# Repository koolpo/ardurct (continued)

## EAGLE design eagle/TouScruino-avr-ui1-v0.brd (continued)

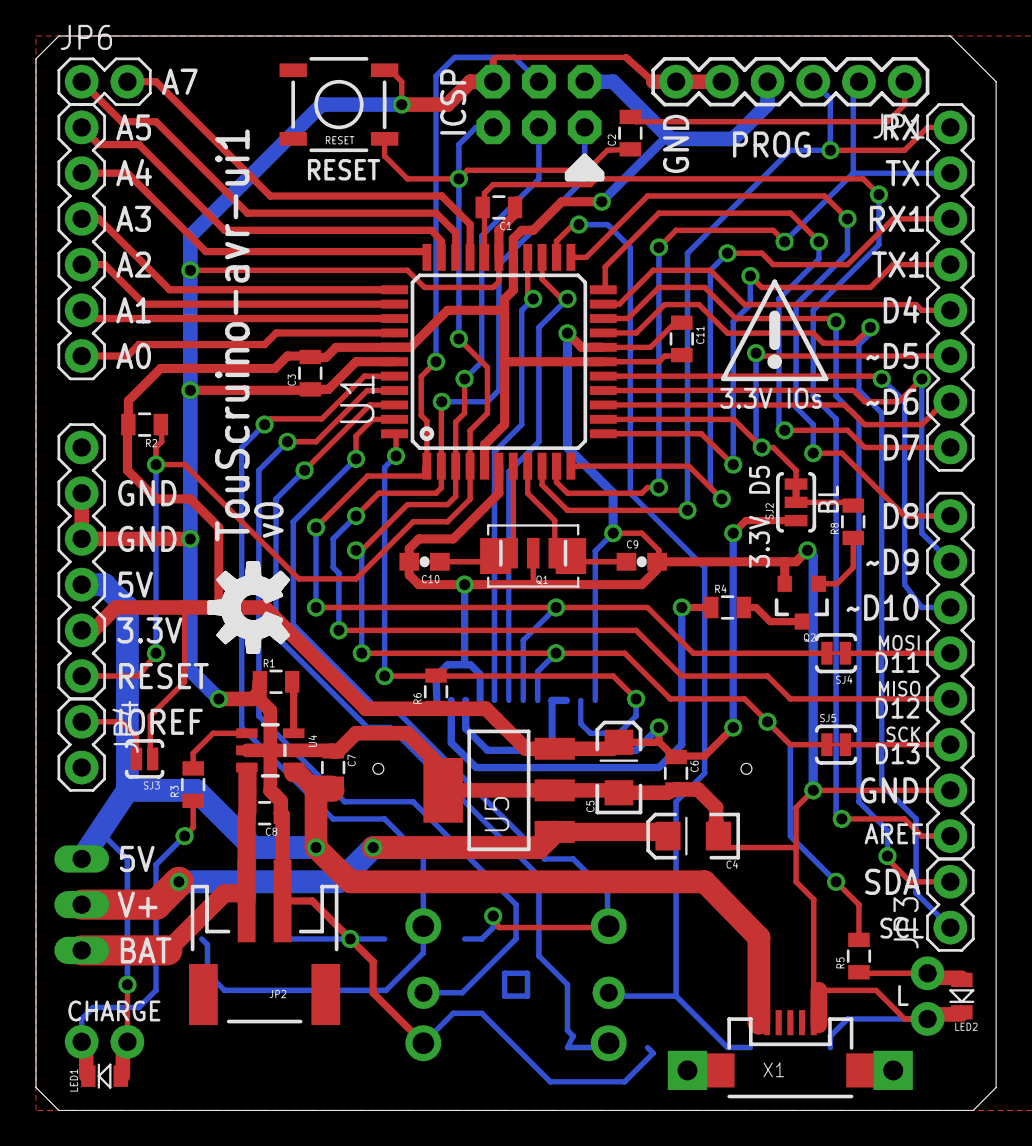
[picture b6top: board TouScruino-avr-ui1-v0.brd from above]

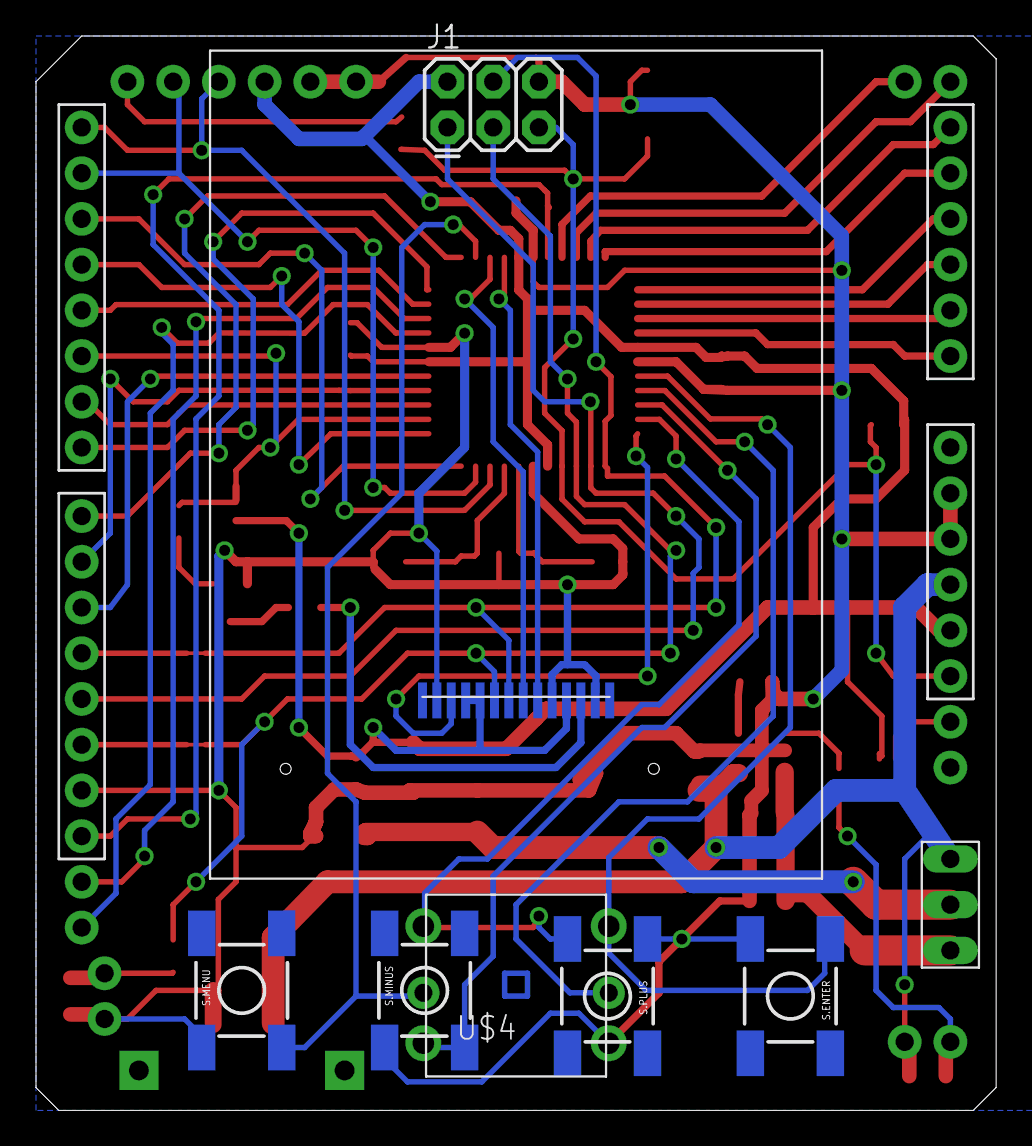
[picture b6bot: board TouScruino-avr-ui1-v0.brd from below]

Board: 2 copper layers, 53.3 x 59.7 mm, 49 parts (9 on the bottom side), 53 nets.

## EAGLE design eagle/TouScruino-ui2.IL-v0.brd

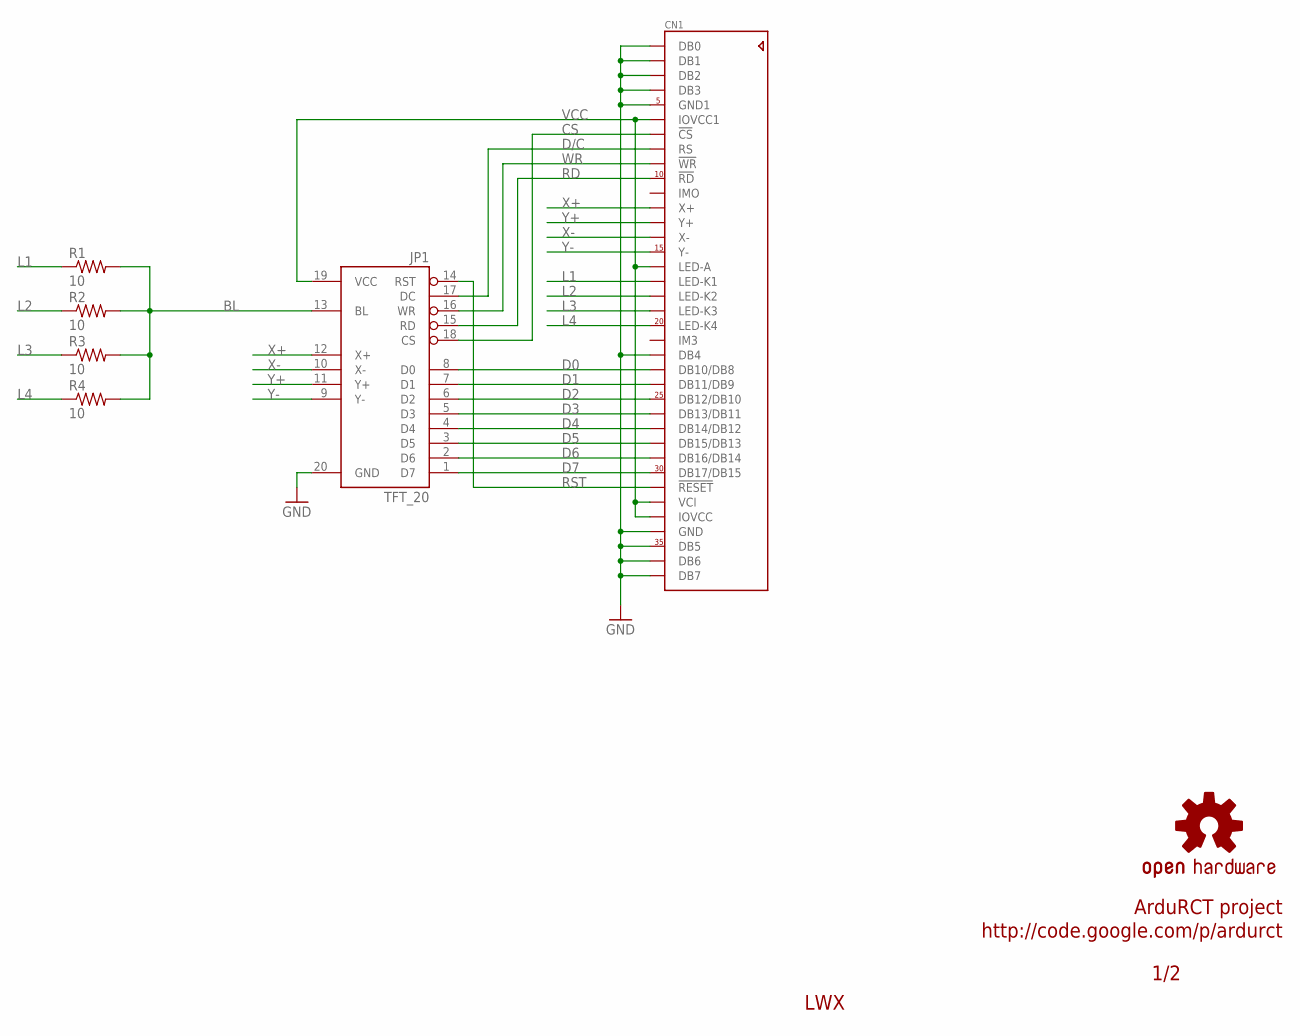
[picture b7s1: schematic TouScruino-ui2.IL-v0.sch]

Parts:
CN1: ILI9325_LCD1.0MM; ILI9325_28INCH_TS
JP1: TFT_20
R1, R2, R3, R4: 10; R0603
U$3: OSHW-LOGOM; OSHW-LOGO-M

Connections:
BL: JP1.13 (BL), R1.2, R2.2, R3.2, R4.2
CS: CN1.7 (!CS), JP1.18 (CS)
D0: CN1.23 (DB10/DB8), JP1.8 (D0)
D1: CN1.24 (DB11/DB9), JP1.7 (D1)
D2: CN1.25 (DB12/DB10), JP1.6 (D2)
D3: CN1.26 (DB13/DB11), JP1.5 (D3)
D4: CN1.27 (DB14/DB12), JP1.4 (D4)
D5: CN1.28 (DB15/DB13), JP1.3 (D5)
D6: CN1.29 (DB16/DB14), JP1.2 (D6)
D7: CN1.30 (DB17/DB15), JP1.1 (D7)
D/C: CN1.8 (RS), JP1.17 (DC)
GND: CN1.1 (DB0), CN1.2 (DB1), CN1.3 (DB2), CN1.4 (DB3), CN1.5 (GND1), CN1.22 (DB4), CN1.34 (GND), CN1.35 (DB5), CN1.36 (DB6), CN1.37 (DB7), JP1.20 (GND)
L1: CN1.17 (LED-K1), R1.1
L2: CN1.18 (LED-K2), R2.1
L3: CN1.19 (LED-K3), R3.1
L4: CN1.20 (LED-K4), R4.1
RD: CN1.10 (!RD), JP1.15 (RD)
RST: CN1.31 (!RESET), JP1.14 (RST)
VCC: CN1.6 (IOVCC1), CN1.16 (LED-A), CN1.32 (VCI), CN1.33 (IOVCC), JP1.19 (VCC)
WR: CN1.9 (!WR), JP1.16 (WR)
X+: CN1.12 (X+), JP1.12 (X+)
X-: CN1.14 (X-), JP1.10 (X-)
Y+: CN1.13 (Y+), JP1.11 (Y+)
Y-: CN1.15 (Y-), JP1.9 (Y-)

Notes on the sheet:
LWX
1/2
ArduRCT project
http://code.google.com/p/ardurct

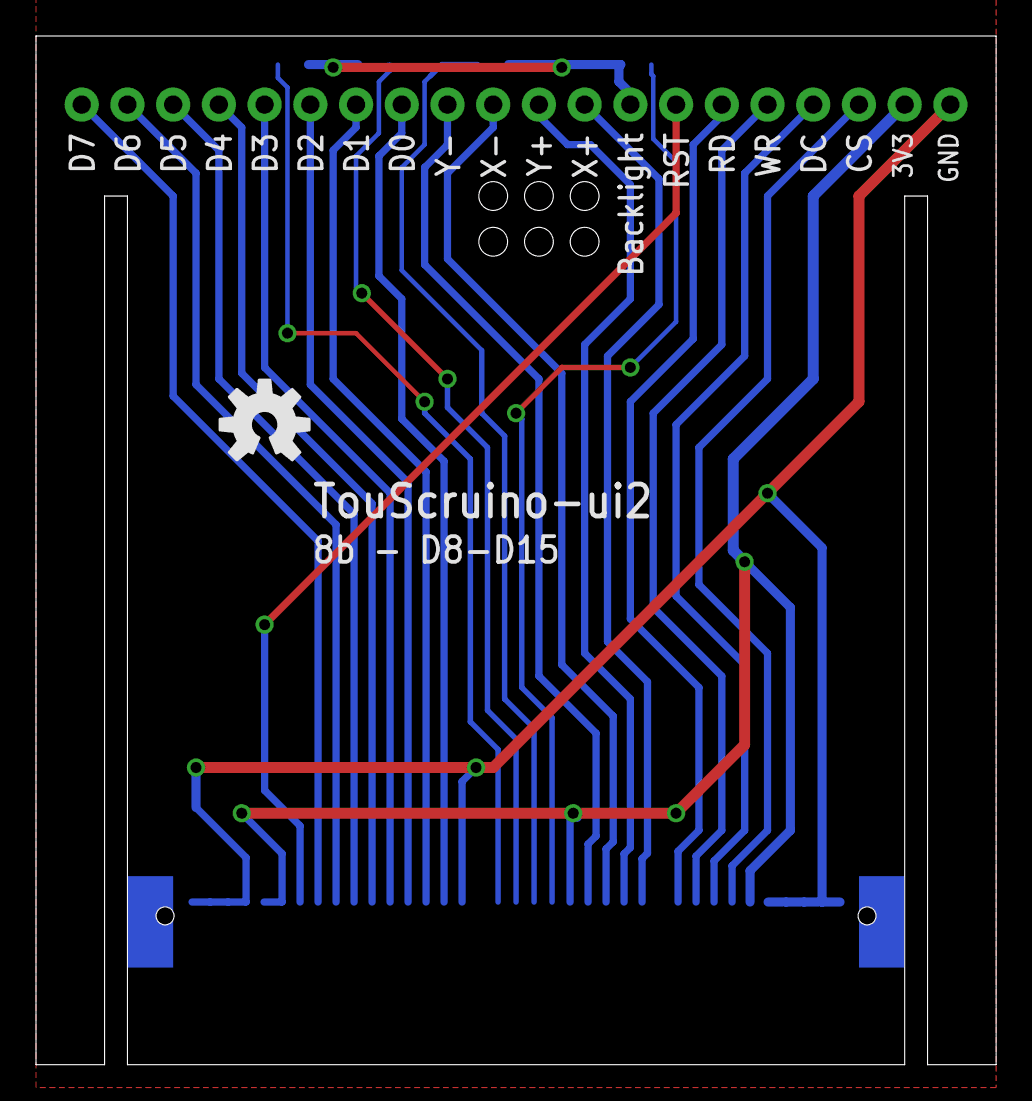
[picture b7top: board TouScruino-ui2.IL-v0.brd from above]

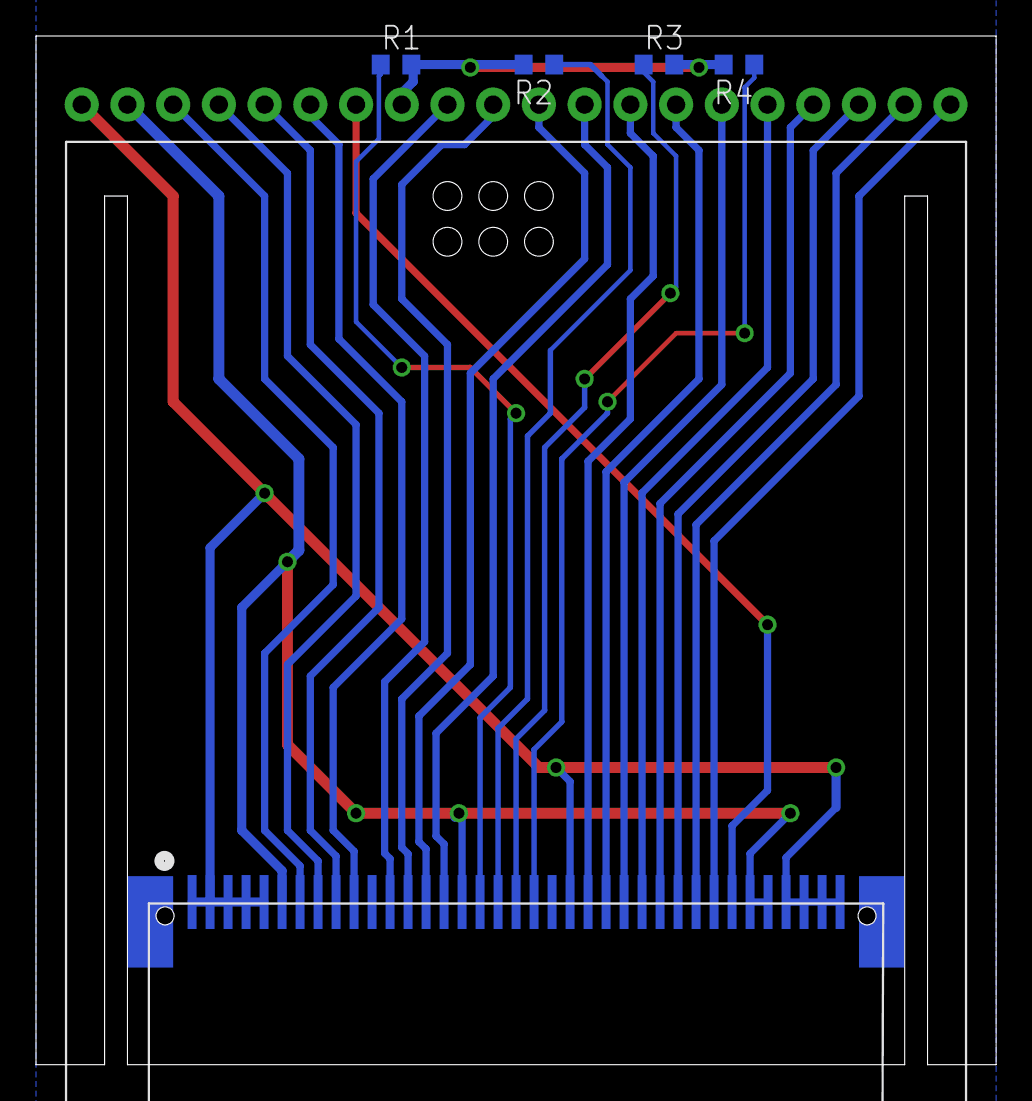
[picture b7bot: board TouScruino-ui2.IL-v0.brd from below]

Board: 2 copper layers, 53.3 x 57.1 mm, 7 parts (6 on the bottom side), 24 nets.

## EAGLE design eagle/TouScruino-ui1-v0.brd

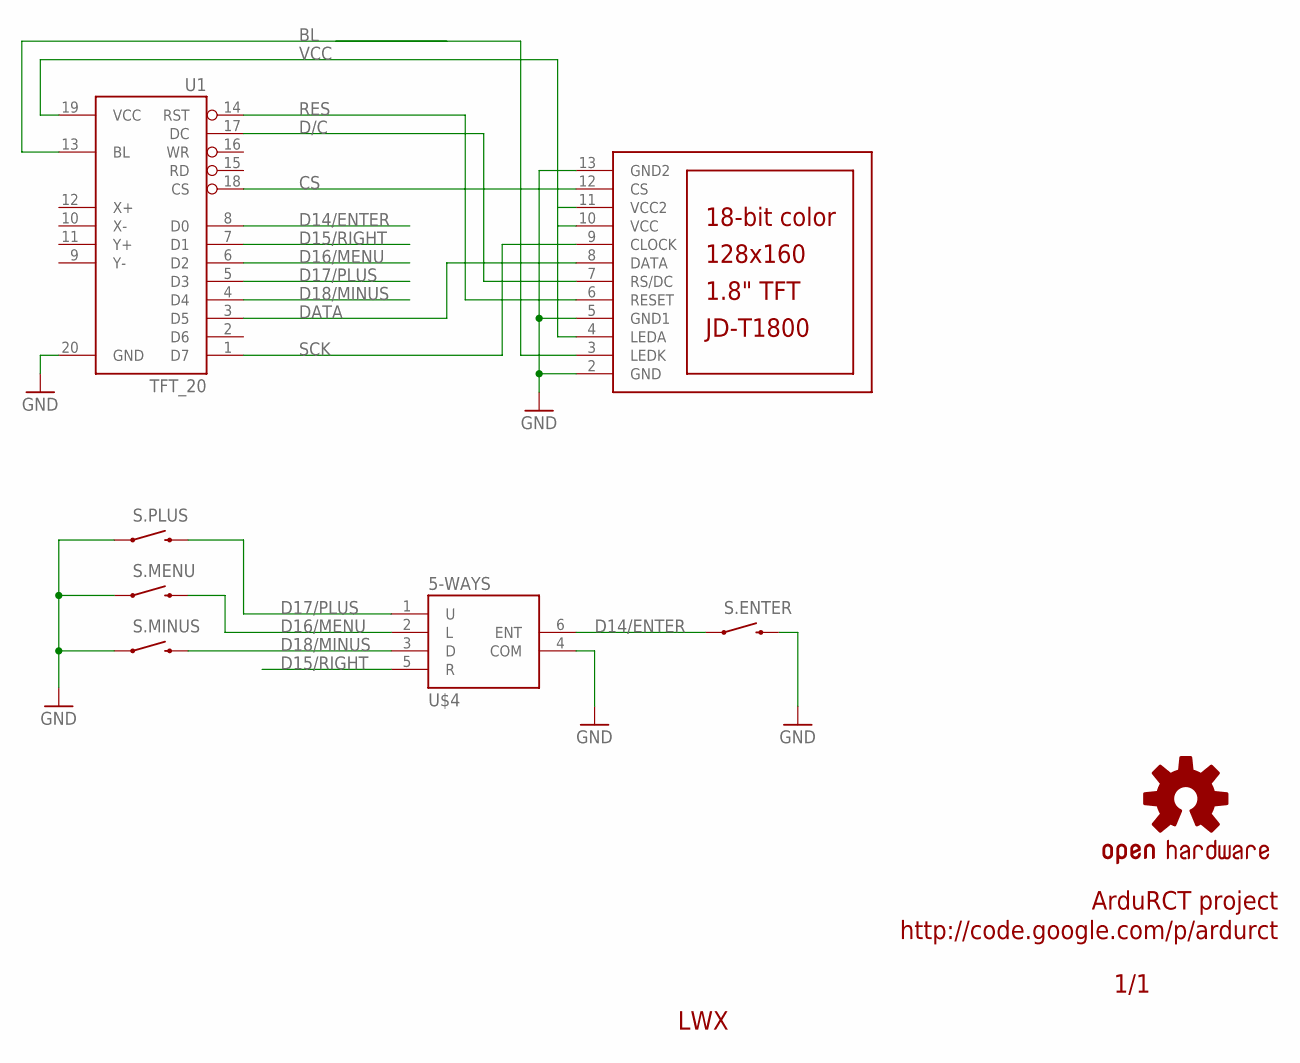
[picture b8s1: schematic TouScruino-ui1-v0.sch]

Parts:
LCD1: JD-T1800
S.ENTER, S.MENU, S.MINUS, S.PLUS: SWITCH_SMD; TACTILE_SWITCH_SMD
U1: TFT_20
U$3: OSHW-LOGOM; OSHW-LOGO-M
U$4: 5-WAYS; 5-WAYS_ALPS

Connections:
BL: LCD1.3 (LEDK), U1.13 (BL)
CS: LCD1.12 (CS), U1.18 (CS)
D14/ENTER: S.ENTER.1, U1.8 (D0), U$4.6 (ENT)
D15/RIGHT: U1.7 (D1), U$4.5 (R)
D16/MENU: S.MENU.3 (2), U1.6 (D2), U$4.2 (L)
D17/PLUS: S.PLUS.3 (2), U1.5 (D3), U$4.1 (U)
D18/MINUS: S.MINUS.3 (2), U1.4 (D4), U$4.3 (D)
D/C: LCD1.7 (RS/DC), U1.17 (DC)
DATA: LCD1.8 (DATA), U1.3 (D5)
GND: LCD1.2 (GND), LCD1.5 (GND1), LCD1.13 (GND2), S.ENTER.3 (2), S.MENU.1, S.MINUS.1, S.PLUS.1, U1.20 (GND), U$4.4 (COM)
RES: LCD1.6 (RESET), U1.14 (RST)
SCK: LCD1.9 (CLOCK), U1.1 (D7)
VCC: LCD1.4 (LEDA), LCD1.10 (VCC), LCD1.11 (VCC2), U1.19 (VCC)

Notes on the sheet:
LWX
1/1
ArduRCT project
http://code.google.com/p/ardurct

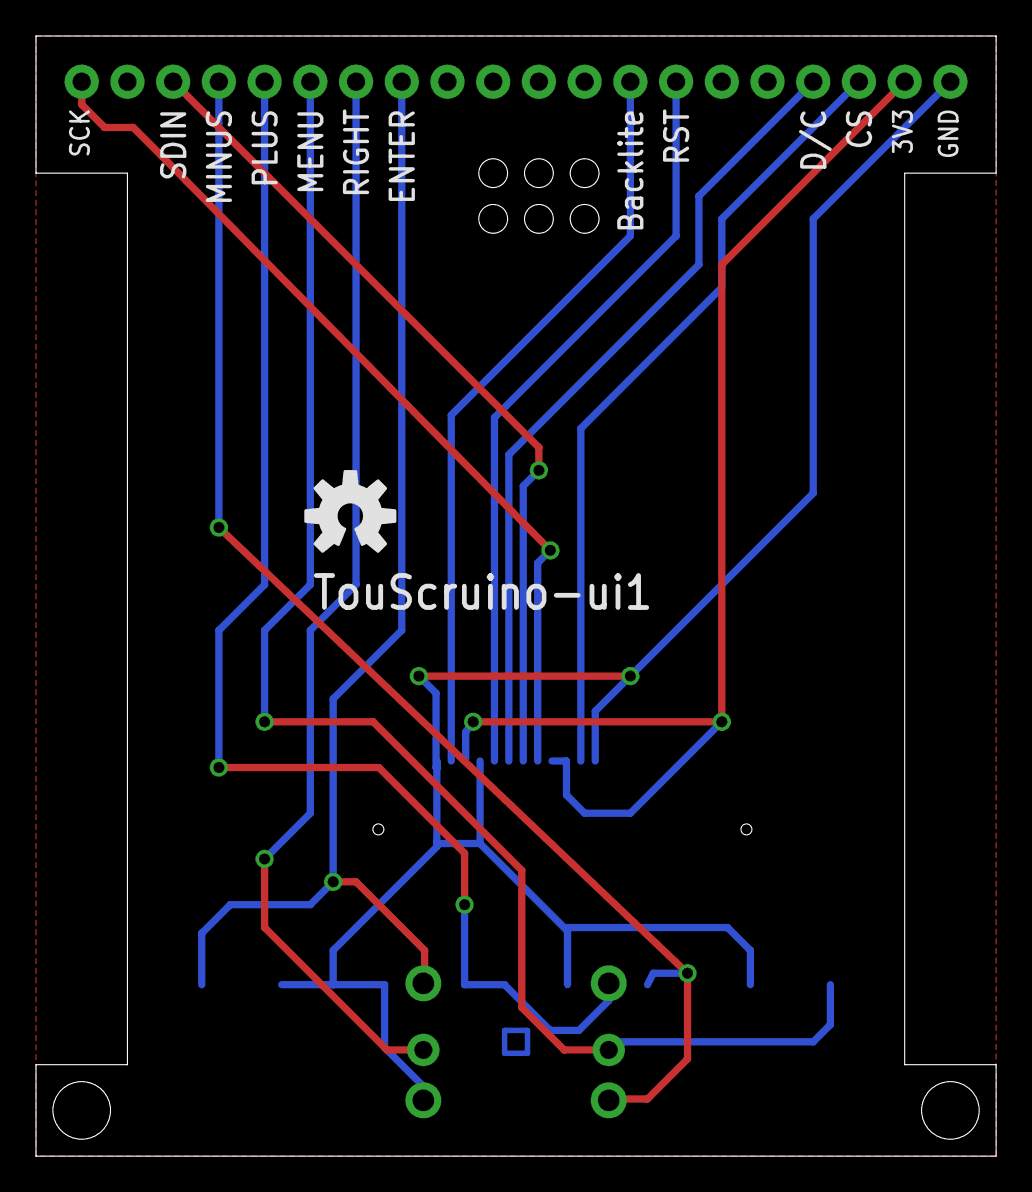
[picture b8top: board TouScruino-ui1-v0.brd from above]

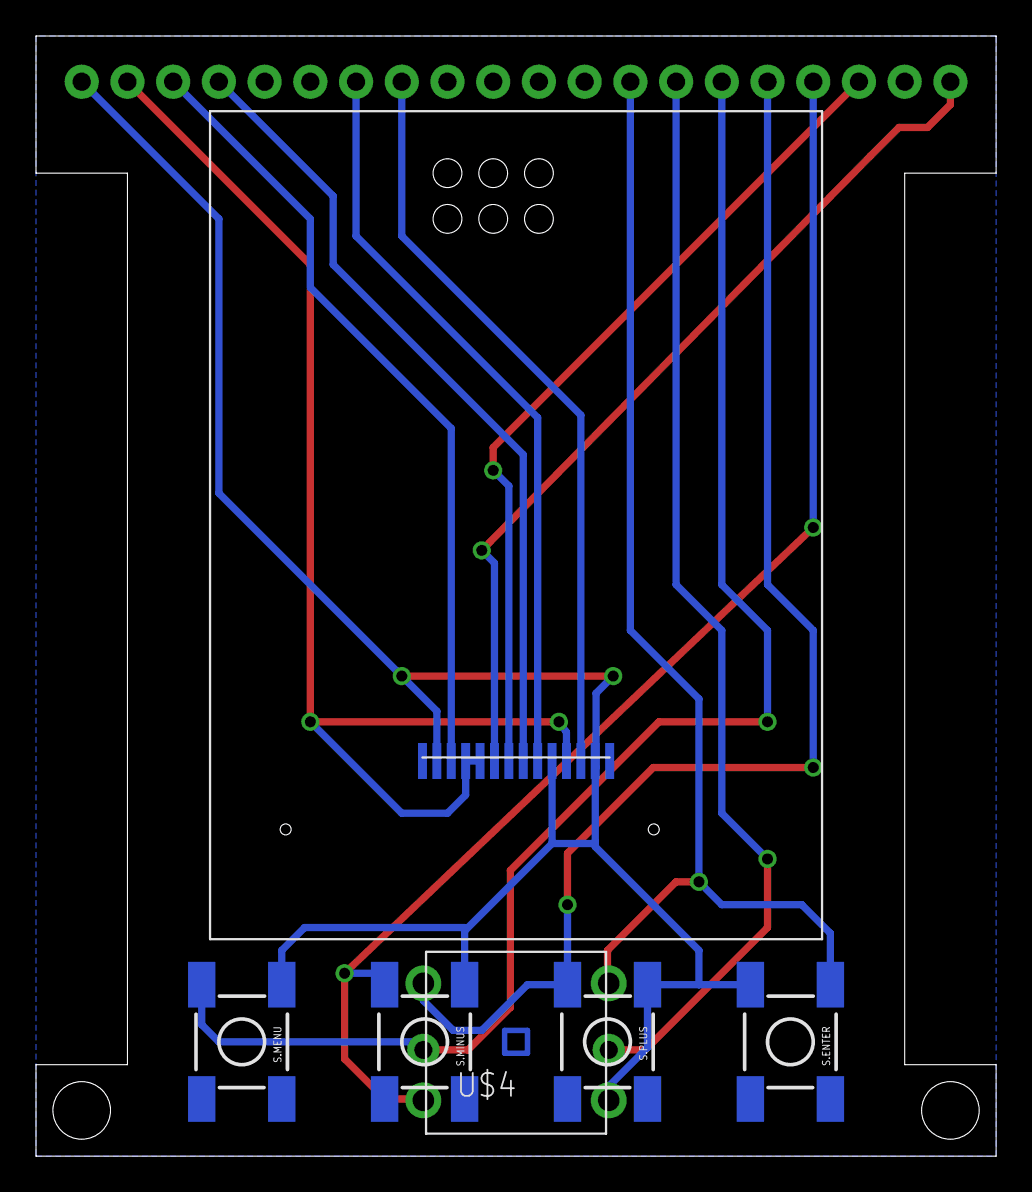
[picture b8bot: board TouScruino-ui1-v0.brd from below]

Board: 2 copper layers, 53.3 x 62.2 mm, 8 parts (7 on the bottom side), 13 nets.

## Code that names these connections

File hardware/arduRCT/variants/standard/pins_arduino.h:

/*
  pins_arduino.h - Pin definition functions for Arduino
  Part of Arduino - http://www.arduino.cc/

  Copyright (c) 2007 David A. Mellis

  This library is free software; you can redistribute it and/or
  modify it under the terms of the GNU Lesser General Public
  License as published by the Free Software Foundation; either
  version 2.1 of the License, or (at your option) any later version.

  This library is distributed in the hope that it will be useful,
  but WITHOUT ANY WARRANTY; without even the implied warranty of
  MERCHANTABILITY or FITNESS FOR A PARTICULAR PURPOSE.  See the GNU
  Lesser General Public License for more details.

  You should have received a copy of the GNU Lesser General
  Public License along with this library; if not, write to the
  Free Software Foundation, Inc., 59 Temple Place, Suite 330,
  Boston, MA  02111-1307  USA

  $Id: wiring.h 249 2007-02-03 16:52:51Z mellis $
*/

#ifndef Pins_Arduino_h
#define Pins_Arduino_h

#include <avr/pgmspace.h>

#define NUM_DIGITAL_PINS            32
#define NUM_ANALOG_INPUTS           8
#define analogInputToDigitalPin(p)  ((p < 8) ? (p) + 24 : -1)
#define digitalPinHasPWM(p)         ((p) == 5 || (p) == 6 || (p) == 9 || (p) == 10 || (p) == 11 || (p) == 17 || (p) == 18)

const static uint8_t SS   = 18;
const static uint8_t MOSI = 11;
const static uint8_t MISO = 12;
const static uint8_t SCK  = 13;

const static uint8_t SDA = 20;
const static uint8_t SCL = 19;
const static uint8_t LED_BUILTIN = 13;

const static uint8_t A0 = 24;
const static uint8_t A1 = 25;
const static uint8_t A2 = 26;
const static uint8_t A3 = 27;
const static uint8_t A4 = 28;
const static uint8_t A5 = 29;
const static uint8_t A6 = 30;
const static uint8_t A7 = 31;

// Only pins available for RECEIVE (TRANSMIT can be on any pin):
// I've deliberately left out pin mapping to the Hardware USARTs
// and also the analog pins: that already makes for 20 RECEIVE pins !

#define digitalPinToPCICR(p)    (((p) >= 4 && (p) <= 23) ? (&PCICR) : ((uint8_t *)0))
#define digitalPinToPCICRbit(p) ( ((p) == 5 || (p) == 6 || (p) == 9 || (p) == 10) ? 3 : \
								( ((p) >= 11 && (p) <= 18) ? 1 : 2 ))
#define digitalPinToPCMSK(p)    ( ((p) == 5 || (p) == 6 || (p) == 9 || (p) == 10) ? (&PCMSK3) : \
								( ((p) >= 11 && (p) <= 18) ? (&PCMSK1) : \
								( ((p) >= 4 && (p) <= 23) ?	(&PCMSK2) : ((uint8_t *)0) )))
#define digitalPinToPCMSKbit(p) ( ((p) == 5 || (p) == 6) ? (p)-1 : \
								( ((p) == 9 || (p) == 10) ? (p)-3 : \
								( ((p) == 4) ? (p)-2 : \
								( ((p) == 7 || (p) == 8) ? (p)-4 : \
								( ((p) >= 11 || (p) <= 13) ? (p)-6 : \
								( ((p) >= 14 || (p) <= 18) ? (p)-14 : \
								( ((p) == 19 || (p) == 20) ? (p)-19 : \
								( ((p) >= 21 || (p) <= 23) ? (p)-16 : 0) )))))))

#ifdef ARDUINO_MAIN

// these arrays map port names (e.g. port B) to the
// appropriate addresses for various functions (e.g. reading
// and writing)
const uint16_t PROGMEM port_to_mode_PGM[] = {
	NOT_A_PORT,
	(uint16_t) &DDRA,
	(uint16_t) &DDRB,
	(uint16_t) &DDRC,
	(uint16_t) &DDRD,
};

const uint16_t PROGMEM port_to_output_PGM[] = {
	NOT_A_PORT,
	(uint16_t) &PORTA,
	(uint16_t) &PORTB,
	(uint16_t) &PORTC,
	(uint16_t) &PORTD,
};

const uint16_t PROGMEM port_to_input_PGM[] = {
	NOT_A_PORT,
	(uint16_t) &PINA,
	(uint16_t) &PINB,
	(uint16_t) &PINC,
	(uint16_t) &PIND,
};

const uint8_t PROGMEM digital_pin_to_port_PGM[] = {
	PD,		// PD0 -  D0 / RX
	PD,		// PD1 -  D1 / TX
	PD,		// PD2 -  D2 / RX2
	PD,		// PD3 -  D3 / TX2
	PC,		// PC2 -  D4
	PD,		// PD4 -  D5 / PWM1
	PD,		// PD5 -  D6 / PWM2
	PC,		// PC3 -  D7
	PC,		// PC4 -  D8
	PD,		// PD6 -  D9 / PWM3
	PD,		// PD7 - D10 / PWM4
	PB,		// PB5 - D11 / MOSI
	PB,		// PB6 - D12 / MISO
	PB,		// PB7 - D13 / SCK / LED_BUILTIN
	PB,		// PB0 - D14
	PB,		// PB1 - D15
	PB,		// PB2 - D16
	PB,		// PB3 - D17 / PWM5
	PB,		// PB4 - D18 / PWM6 / SS
	PC,		// PC0 - D19 / SCL
	PC,		// PC1 - D20 / SDA
	PC,		// PC5 - D21
	PC,		// PC6 - D22
	PC,		// PC7 - D23
	PA,		// PA0 - D24 / A0
	PA,		// PA1 - D25 / A1
	PA,		// PA2 - D26 / A2
	PA,		// PA3 - D27 / A3
	PA,		// PA4 - D28 / A4
	PA,		// PA5 - D29 / A5
	PA,		// PA6 - D30 / A6
	PA,		// PA7 - D31 / A7
};

const uint8_t PROGMEM digital_pin_to_bit_mask_PGM[] = {
	_BV(0),		// PD0 -  D0 / RX
	_BV(1),		// PD1 -  D1 / TX
	_BV(2),		// PD2 -  D2 / RX2
	_BV(3),		// PD3 -  D3 / TX2
	_BV(2),		// PC2 -  D4
	_BV(4),		// PD4 -  D5 / PWM1
	_BV(5),		// PD5 -  D6 / PWM2
	_BV(3),		// PC3 -  D7
	_BV(4),		// PC4 -  D8
	_BV(6),		// PD6 -  D9 / PWM3
	_BV(7),		// PD7 - D10 / PWM4
	_BV(5),		// PB5 - D11 / MOSI
	_BV(6),		// PB6 - D12 / MISO
	_BV(7),		// PB7 - D13 / SCK / LED_BUILTIN
	_BV(0),		// PB0 - D14
	_BV(1),		// PB1 - D15
	_BV(2),		// PB2 - D16
	_BV(3),		// PB3 - D17 / PWM5
	_BV(4),		// PB4 - D18 / PWM6 / SS
	_BV(0),		// PC0 - D19 / SCL
	_BV(1),		// PC1 - D20 / SDA
	_BV(5),		// PC5 - D21
	_BV(6),		// PC6 - D22
	_BV(7),		// PC7 - D23
	_BV(0),		// PA0 - D24 / A0
	_BV(1),		// PA1 - D25 / A1
	_BV(2),		// PA2 - D26 / A2
	_BV(3),		// PA3 - D27 / A3
	_BV(4),		// PA4 - D28 / A4
	_BV(5),		// PA5 - D29 / A5
	_BV(6),		// PA6 - D30 / A6
	_BV(7),		// PA7 - D31 / A7
};

const uint8_t PROGMEM digital_pin_to_timer_PGM[] = {
	NOT_ON_TIMER,
	NOT_ON_TIMER,
	NOT_ON_TIMER,
	NOT_ON_TIMER,
	NOT_ON_TIMER,
	TIMER1B,		// PD4 -  D5 / PWM1
	TIMER1A,		// PD5 -  D6 / PWM2
	NOT_ON_TIMER,
	NOT_ON_TIMER,
	TIMER2B,		// PD6 -  D9 / PWM3
	TIMER2A,		// PD7 - D10 / PWM4
	NOT_ON_TIMER,
	NOT_ON_TIMER,
	NOT_ON_TIMER,
	NOT_ON_TIMER,
	NOT_ON_TIMER,
	NOT_ON_TIMER,
	TIMER0A,		// PB3 - D17 / PWM5
	TIMER0B,		// PB4 - D18 / PWM6 / SS
	NOT_ON_TIMER,
	NOT_ON_TIMER,
	NOT_ON_TIMER,
	NOT_ON_TIMER,
	NOT_ON_TIMER,
	NOT_ON_TIMER,
	NOT_ON_TIMER,
	NOT_ON_TIMER,
	NOT_ON_TIMER,
	NOT_ON_TIMER,
	NOT_ON_TIMER,
	NOT_ON_TIMER,
	NOT_ON_TIMER,
};

#endif

#endif

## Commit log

2011-04-11 1 screen version
2011-04-11 Added comments
2011-04-11 Added a newline in the output
2011-04-18 Fix: drawProgressBar
2011-04-18 First revision: display tests
2011-04-26 Initial version
2011-04-26 Updated the refresh rate for servos to 50Hz
2011-05-30 ServoManager v1.3: faster output
2011-06-10 Added blender and eagle files
2011-12-09 Adjusted silkscreen to show D17 and D18 as PWM
2015-05-05 Migrating wiki contents from Google Code
